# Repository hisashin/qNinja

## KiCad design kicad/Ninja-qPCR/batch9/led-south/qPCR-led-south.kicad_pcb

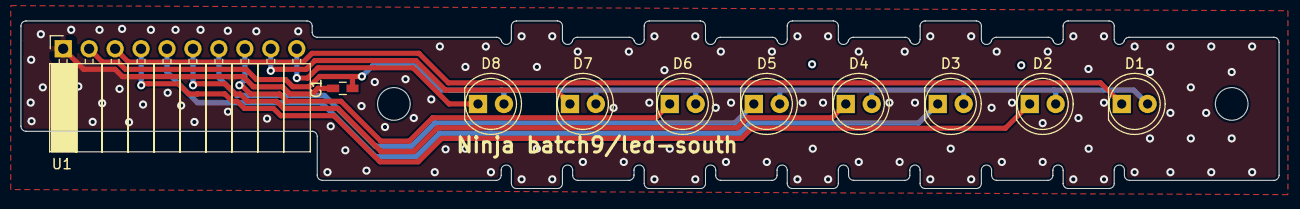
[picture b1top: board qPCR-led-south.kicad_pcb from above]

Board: 2 copper layers, 123.1 x 16.4 mm, 10 parts (0 on the bottom side), 10 nets.

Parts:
C1: C; C_0603_HandSoldering
D1, D2, D3, D4, D5, D6, D7, D8: LED; LED_D5.0mm
U1: Conn_02x05; Socket_Strip_Angled_1x10_Pitch2.54mm

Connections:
GND: C1.2, U1.1
OUT1: D1.1, U1.3
OUT2: D2.1, U1.4
OUT3: D3.1, U1.5
OUT4: D4.1, U1.6
OUT5: D5.1, U1.7
OUT6: D6.1, U1.8
OUT7: D7.1, U1.9
OUT8: D8.1, U1.10
VCC: C1.1, D1.2, D2.2, D3.2, D4.2, D5.2, D6.2, D7.2, D8.2, U1.2

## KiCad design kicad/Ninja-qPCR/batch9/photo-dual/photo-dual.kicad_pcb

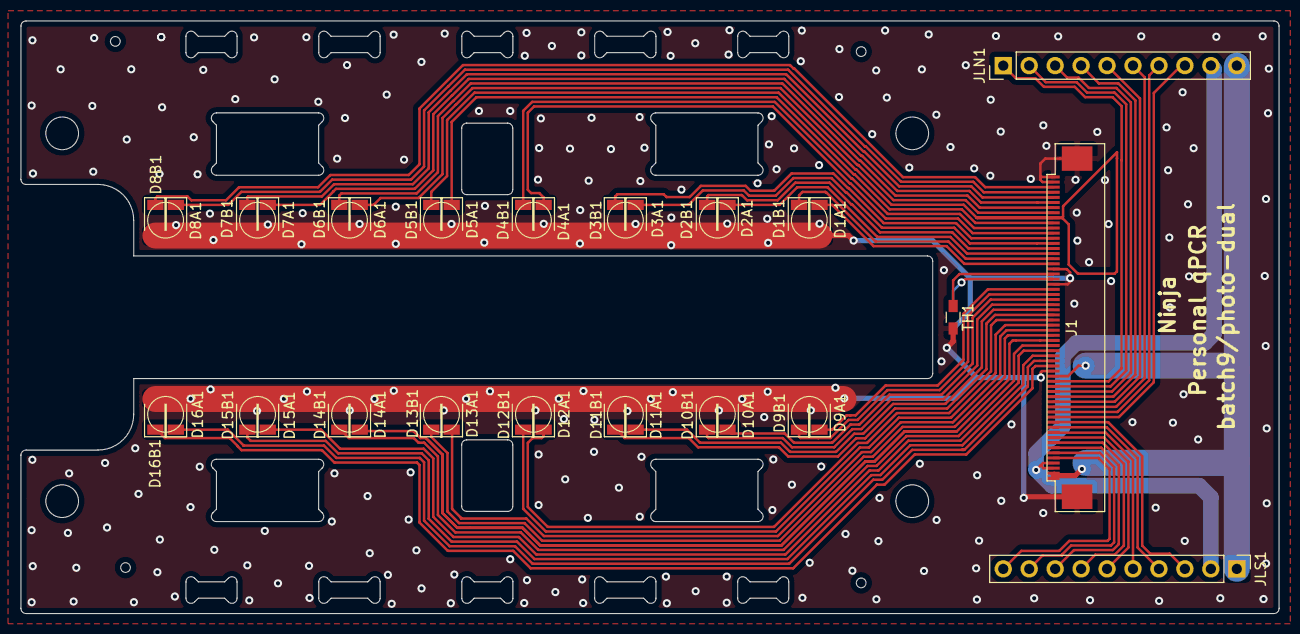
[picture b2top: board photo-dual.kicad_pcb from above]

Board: 2 copper layers, 123.1 x 58.0 mm, 37 parts (1 on the bottom side), 53 nets.

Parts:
D1A1, D1B1, D2A1, D2B1, D3A1, D3B1, D4A1, D4B1, D5A1, D5B1, D6A1, D6B1, D7A1, D7B1, D8A1, D8B1, D9A1, D9B1, D10A1, D10B1, D11A1, D11B1, D12A1, D12B1, D13A1, D13B1, D14A1, D14B1, D15A1, D15B1, D16A1, D16B1: D_Photo; D_1206
J1: Conn_01x60_Male; FFC_60_Ali_HUISHUNFA
JLN1: Conn_01x10_Male; Pin_Header_Straight_1x10_Pitch2.54mm
JLS1: Conn_01x10_Male; Pin_Header_Straight_1x10_Pitch2.54mm
TH1, TH2: Thermistor; R_0603_HandSoldering

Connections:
/N_LED_OUT9: J1.13, JLN1.8
/N_LED_OUT10: J1.14, JLN1.7
/N_LED_OUT11: J1.15, JLN1.6
/N_LED_OUT12: J1.16, JLN1.5
/N_LED_OUT13: J1.17, JLN1.4
/N_LED_OUT14: J1.18, JLN1.3
/N_LED_OUT15: J1.19, JLN1.2
/N_LED_OUT16: J1.20, JLN1.1
/N_PD_OUT1: D1A1.1, J1.43
/N_PD_OUT2: D1B1.1, J1.44
/N_PD_OUT3: D2A1.1, J1.45
/N_PD_OUT4: D2B1.1, J1.46
/N_PD_OUT5: D3A1.1, J1.47
/N_PD_OUT6: D3B1.1, J1.48
/N_PD_OUT7: D4A1.1, J1.49
/N_PD_OUT8: D4B1.1, J1.50
/N_PD_OUT9: D5A1.1, J1.51
/N_PD_OUT10: D5B1.1, J1.52
/N_PD_OUT11: D6A1.1, J1.53
/N_PD_OUT12: D6B1.1, J1.54
/N_PD_OUT13: D7A1.1, J1.55
/N_PD_OUT14: D7B1.1, J1.56
/N_PD_OUT15: D8A1.1, J1.57
/N_PD_OUT16: D8B1.1, J1.58
/S_LED_OUT1: J1.12, JLS1.3
/S_LED_OUT2: J1.11, JLS1.4
/S_LED_OUT3: J1.10, JLS1.5
/S_LED_OUT4: J1.9, JLS1.6
/S_LED_OUT5: J1.8, JLS1.7
/S_LED_OUT6: J1.7, JLS1.8
/S_LED_OUT7: J1.6, JLS1.9
/S_LED_OUT8: J1.5, JLS1.10
/S_PD_OUT1: D9A1.1, J1.38
/S_PD_OUT2: D9B1.1, J1.37
/S_PD_OUT3: D10A1.1, J1.36
/S_PD_OUT4: D10B1.1, J1.35
/S_PD_OUT5: D11A1.1, J1.34
/S_PD_OUT6: D11B1.1, J1.33
/S_PD_OUT7: D12A1.1, J1.32
/S_PD_OUT8: D12B1.1, J1.31
/S_PD_OUT9: D13A1.1, J1.30
/S_PD_OUT10: D13B1.1, J1.29
/S_PD_OUT11: D14A1.1, J1.28
/S_PD_OUT12: D14B1.1, J1.27
/S_PD_OUT13: D15A1.1, J1.26
/S_PD_OUT14: D15B1.1, J1.25
/S_PD_OUT15: D16A1.1, J1.24
/S_PD_OUT16: D16B1.1, J1.23
GNDA: D1A1.2, D1B1.2, D2A1.2, D2B1.2, D3A1.2, D3B1.2, D4A1.2, D4B1.2, D5A1.2, D5B1.2, D6A1.2, D6B1.2, D7A1.2, D7B1.2, D8A1.2, D8B1.2, D9A1.2, D9B1.2, D10A1.2, D10B1.2, D11A1.2, D11B1.2, D12A1.2, D12B1.2, D13A1.2, D13B1.2, D14A1.2, D14B1.2, D15A1.2, D15B1.2, D16A1.2, D16B1.2, J1.22, J1.39, J1.42, J1.59, J1.60, J1.G1, J1.G2, TH1.2, TH2.2
GNDL: J1.1, J1.2, J1.21, JLN1.10, JLS1.1
unnamed: J1.40, TH2.1
unnamed: J1.41, TH1.1
VCCL: J1.3, J1.4, JLN1.9, JLS1.2
